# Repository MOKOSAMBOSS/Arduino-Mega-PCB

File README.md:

# Arduino Mega PCB

This repository contains a custom Arduino Mega compatible PCB designed in KiCad 10.

## Contents
- KiCad schematic (.kicad_sch)
- KiCad PCB layout (.kicad_pcb)
- Gerber files
- Drill files
- Bill of Materials (BOM)
- Project files

## Software
- KiCad 10

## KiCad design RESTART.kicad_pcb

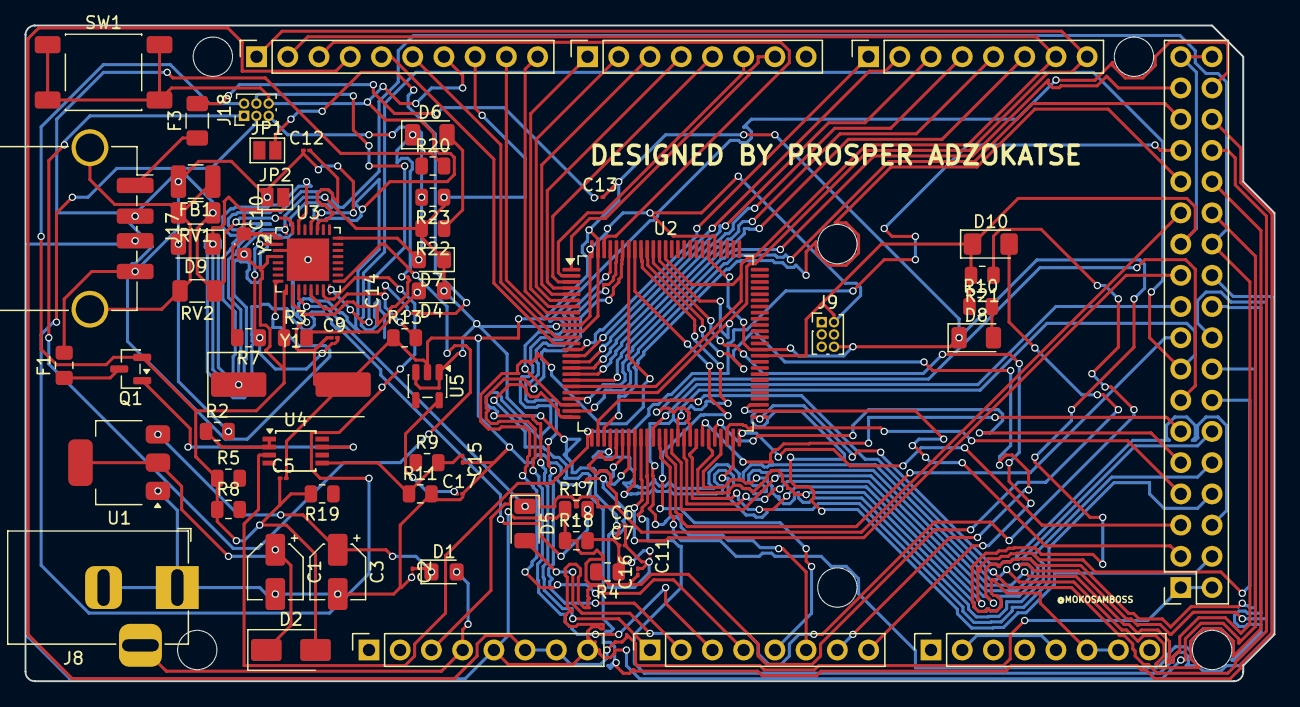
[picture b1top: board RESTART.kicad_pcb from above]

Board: 2 copper layers, 101.6 x 53.3 mm, 74 parts (0 on the bottom side), 88 nets.

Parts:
C1, C3: C_Polarized; CP_Elec_4x3.9
C2, C5, C6, C7, C9, C10, C11, C12, C13, C14, C15, C16, C17: C; C_01005_0402Metric
D1, D4, D7: D; D_0805_2012Metric_Pad1.15x1.40mm_HandSolder
D2: B120-E3; D_SMA
D5, D6, D8, D9: LED; LED_1206_3216Metric
D10: D; D_1206_3216Metric_Pad1.42x1.75mm_HandSolder
F1: Polyfuse; Fuse_0805_2012Metric_Pad1.15x1.40mm_HandSolder
F3: Polyfuse; Fuse_1206_3216Metric
FB1: FerriteBead; L_1210_3225Metric
J1: Power; PinSocket_1x08_P2.54mm_Vertical
J2: PWM; PinSocket_1x10_P2.54mm_Vertical
J3, J5: Analog; PinSocket_1x08_P2.54mm_Vertical
J4: PWM; PinSocket_1x08_P2.54mm_Vertical
J6: Communication; PinSocket_1x08_P2.54mm_Vertical
J7: Digital; PinSocket_2x18_P2.54mm_Vertical
J8: Barrel_Jack_Switch; BarrelJack_Horizontal
J9, J18: Conn_02x03_Odd_Even; PinHeader_2x03_P1.00mm_Vertical
J17: USB_B_Micro; USB_A_TE_292303-7_Horizontal
JP1, JP2: SolderJumper_2_Open; SolderJumper-2_P1.3mm_Open_Pad1.0x1.5mm
MH1, MH2, MH3, MH4, MH5, MH6: MountingHole_3.2mm
Q1: FDN340P; SOT-23
R2, R3, R4, R5, R7, R8, R9, R10, R11, R13, R17, R18, R19, R20, R21, R22, R23: R; R_0805_2012Metric
RV1, RV2: Varistor; Fuse_1206_3216Metric
SW1: SW_MEC_5E; SW_Push_1P1T_NO_E-Switch_TL3301NxxxxxG
U1: NCP1117-5.0_SOT223; SOT-223-3_TabPin2
U2: ATmega2560-16A; TQFP-100_14x14mm_P0.5mm
U3: ATmega16U2-M; QFN-32-1EP_5x5mm_P0.5mm_EP3.45x3.45mm
U4: LMV358; TSSOP-8_3x3mm_P0.65mm
U5: LP2985-3.3; SOT-23-5
Y1: Resonator; Crystal_SMD_HC49-SD
Y2: Crystal; Crystal_SMD_MicroCrystal_CM9V-T1A-2Pin_1.6x1.0mm_HandSolder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

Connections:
+5V: C5.1, C6.1, C7.1, C11.1, D2.2 (A), D4.1 (K_1), D7.1 (K), D10.1 (K_1), J2.8, J7.23, J7.35, J7.36, J9.2, J18.2, Q1.2 (S), R3.1, R4.1, R5.1, R8.1, R10.1, R18.2, R19.2, R21.2, R22.2, R23.1, U2.10 (VCC), U2.31 (VCC), U2.61 (VCC), U2.80 (VCC), U2.100 (AVCC), U3.4 (VCC), U3.9 (PD3), U3.29 (D+), U3.32 (AVCC), U5.1 (VIN), U5.3 (ON/~OFF), Y2.2
/22: J7.33, U2.22 (PB3)
/24: J7.31, U2.24 (PB5)
/26: J7.29, U2.26 (PB7), U4.3 (+)
/27: J7.30, U2.27 (PH7)
/28: J7.27, U2.28 (PG3)
/29: J7.28, U2.29 (PG4)
/33: J7.24, U2.33 (XTAL2), Y1.1
/35: J7.22, U2.35 (PL0)
/37: J7.20, U2.37 (PL2)
/39: J7.18, U2.39 (PL4)
/40: D5.1 (K), J7.15, U2.40 (PL5), U3.11 (PD5)
/41: J7.16, U2.41 (PL6)
/42: J7.13, U2.42 (PL7)
/43: J7.14, U2.43 (PD0)
/47: J7.10, U2.47 (PD4)
/48: J7.7, U2.48 (PD5)
/49: J7.8, U2.49 (PD6)
/50: J7.5, U2.50 (PD7)
/51: J7.6, U2.51 (PG0)
/53: J7.4, U2.53 (PC0)
/*2: J4.6, U2.2 (PE0)
/*3: J4.5, U2.3 (PE1)
/*4: J4.4, U2.4 (PE2)
/*5: J4.3, U2.5 (PE3)
/*6: J4.2, U2.6 (PE4)
/*7: J4.1, U2.7 (PE5)
/*8: J2.10, U2.8 (PE6)
/*9: J2.9, U2.9 (PE7)
/*12: J2.6, U2.12 (PH0)
/*13: J2.5, U2.13 (PH1)
/*44: J7.11, U2.44 (PD1)
/*45: J7.12, U2.45 (PD2)
/*46: J7.9, U2.46 (PD3)
/*52: J7.3, U2.52 (PG1)
/A0: J3.1, U2.97 (PF0)
/A1: J3.2, U2.96 (PF1)
/A2: J3.3, U2.95 (PF2)
/A3: J3.4, U2.94 (PF3)
/A4: J3.5, U2.93 (PF4)
/A5: J3.6, U2.92 (PF5)
/A6: J3.7, U2.91 (PF6)
/A7: J3.8, U2.90 (PF7)
/A12: J5.2, J5.5
/AREF: J2.3, U2.98 (AREF)
/RX1/19: J6.6, U2.19 (PB0)
/RX2/17: J6.4, U2.17 (PH5)
/RX3/15: J6.2, U2.15 (PH3)
/SCL/21: J2.1, J6.8, U2.21 (PB2), U2.89 (PK0)
/SDA/20: J2.2, J6.7, U2.20 (PB1), U2.88 (PK1)
/TX0/1: J4.7, U2.1 (PG5)
/TX1/18: J6.5, U2.18 (PH6)
/TX2/16: J6.3, U2.16 (PH4)
/TX3/14: J6.1, U2.14 (PH2)
/Vin: J1.5, J1.8, J7.26, J17.2 (D-), J17.3 (D+), R17.1, R18.1, RV1.1, RV2.1, U3.31 (UVCC)
/~RESET: J1.3, J7.25, U2.30 (~RESET)
GND: J1.6, J1.7, J2.4, J7.1, J7.2
GNDD: C1.2, C2.2, C3.2, C5.2, C6.2, C7.2, C9.1, C10.1, C11.2, C13.2, C15.2, C16.2, C17.2, D8.1 (K), D9.1 (K), J2.7, J5.6, J5.7, J8.1, J8.2, J9.6, J18.6, JP2.2 (B), R11.2, R13.1, SW1.1, SW1.2, U1.1 (GND), U2.11 (GND), U2.32 (GND), U2.62 (GND), U2.81 (GND), U2.99 (GND), U3.3 (GND), U3.33 (GND), U5.2 (GND), Y1.2
unnamed: D1.2 (A), J1.4, J8.3
unnamed: C2.1, C3.1, D1.1 (K), U1.3 (VI)
unnamed: C1.1, D2.1 (K), U1.2 (VO)
unnamed: D5.2 (A), R21.1
unnamed: D6.2 (A), R22.1
unnamed: D6.1 (K), U3.10 (PD4)
unnamed: D7.2 (A), J18.5, R23.2, U3.24 (PC1/~RESET)
unnamed: D8.2 (A), R10.2
unnamed: D9.2 (A), R2.2
unnamed: J7.17, U2.38 (PL3)
unnamed: J7.19, U2.36 (PL1)
unnamed: J7.21, U2.34 (XTAL1)
unnamed: J7.32, U2.25 (PB6)
unnamed: J7.34, U2.23 (PB4)
unnamed: FB1.1, J17.SH (Shield), RV1.2, RV2.2
unnamed: C12.1, F1.2, FB1.2, J17.4 (ID), JP2.1 (A), U3.28 (UGND)
unnamed: F3.1, J17.1 (VBUS)
unnamed: J18.1, U3.17 (PB3)
unnamed: J18.3, U3.15 (PB1)
unnamed: J18.4, U3.16 (PB2)
unnamed: F1.1, Q1.3 (D)
unnamed: Q1.1 (G), U4.7
unnamed: R17.2, U3.30 (D-)
unnamed: C9.2, R7.1, U3.2 (PC0/XTAL2)
unnamed: R20.2, U3.8 (PD2)
unnamed: C12.2, U3.27 (UCAP)
unnamed: C10.2, R7.2, U3.1 (XTAL1), Y2.1
unnamed: C14.1, R13.2, U3.13 (~HWB/PD7)
unnamed: R2.1, U4.1, U4.2 (-)
unnamed: C15.1, R9.2, R11.1, U4.5 (+)
